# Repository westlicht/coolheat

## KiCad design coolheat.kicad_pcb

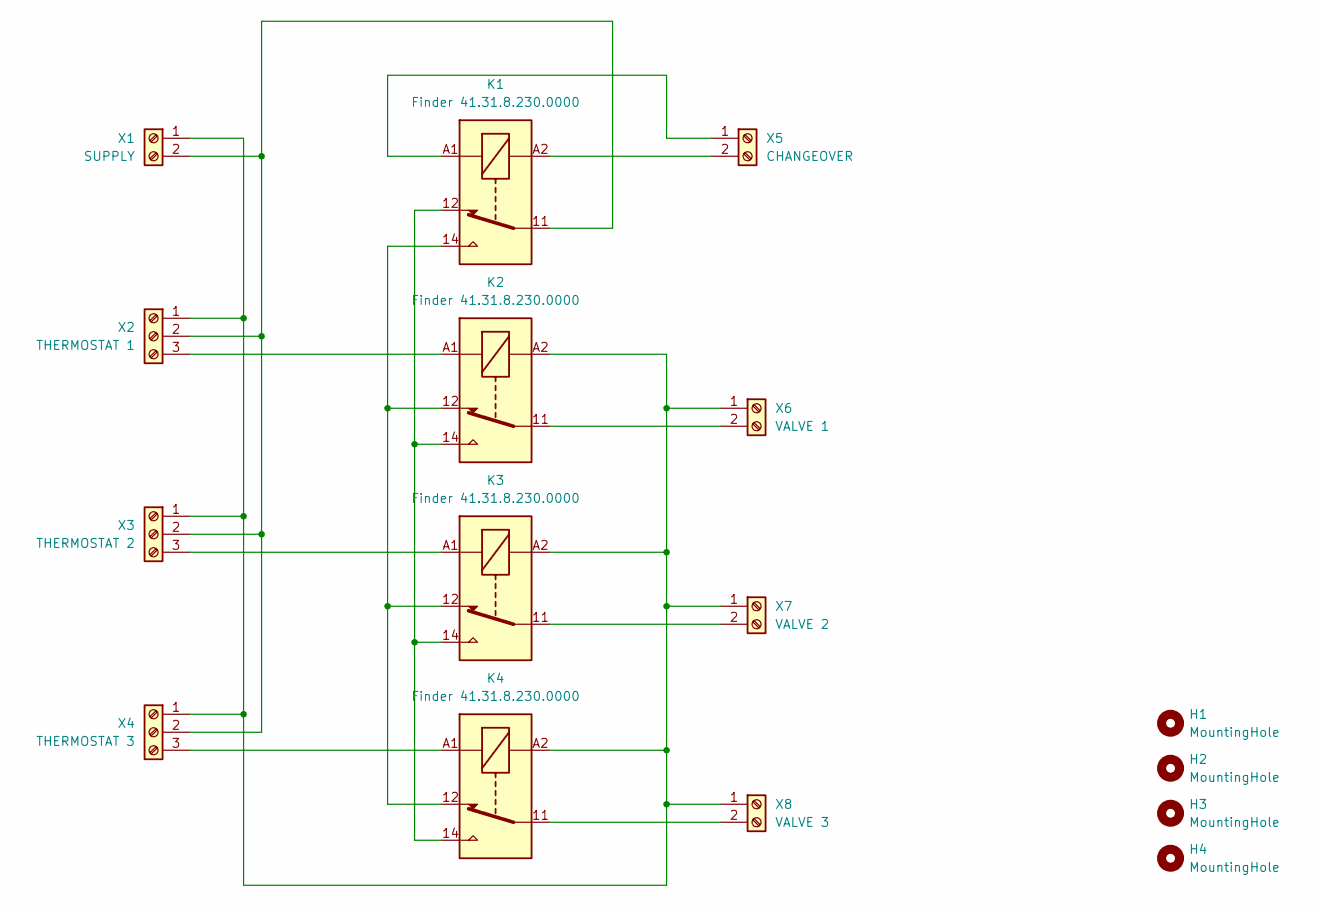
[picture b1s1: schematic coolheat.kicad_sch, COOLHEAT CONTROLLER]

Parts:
H1, H2, H3, H4: MountingHole; MountingHole_4.3mm_M4
K1, K2, K3, K4: Finder 41.31.8.230.0000; Relay_SPDT_Finder_41.31
X1: SUPPLY; TerminalBlock_Phoenix_MKDS-3-2-5.08_1x02_P5.08mm_Horizontal
X2: THERMOSTAT 1; TerminalBlock_Phoenix_MKDS-3-3-5.08_1x03_P5.08mm_Horizontal
X3: THERMOSTAT 2; TerminalBlock_Phoenix_MKDS-3-3-5.08_1x03_P5.08mm_Horizontal
X4: THERMOSTAT 3; TerminalBlock_Phoenix_MKDS-3-3-5.08_1x03_P5.08mm_Horizontal
X5: CHANGEOVER; TerminalBlock_Phoenix_MKDS-3-2-5.08_1x02_P5.08mm_Horizontal
X6: VALVE 1; TerminalBlock_Phoenix_MKDS-3-2-5.08_1x02_P5.08mm_Horizontal
X7: VALVE 2; TerminalBlock_Phoenix_MKDS-3-2-5.08_1x02_P5.08mm_Horizontal
X8: VALVE 3; TerminalBlock_Phoenix_MKDS-3-2-5.08_1x02_P5.08mm_Horizontal

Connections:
unnamed: K1.12, K2.14, K3.14, K4.14
unnamed: K1.14, K2.12, K3.12, K4.12
unnamed: K2.A2, K3.A2, K4.A2, X1.1, X2.1, X3.1, X4.1, X6.1, X7.1, X8.1
unnamed: K1.11, X1.2, X2.2, X3.2, X4.2
unnamed: K2.A1, X2.3
unnamed: K3.A1, X3.3
unnamed: K4.A1, X4.3
unnamed: K1.A1, X5.1
unnamed: K1.A2, X5.2
unnamed: K2.11, X6.2
unnamed: K3.11, X7.2
unnamed: K4.11, X8.2

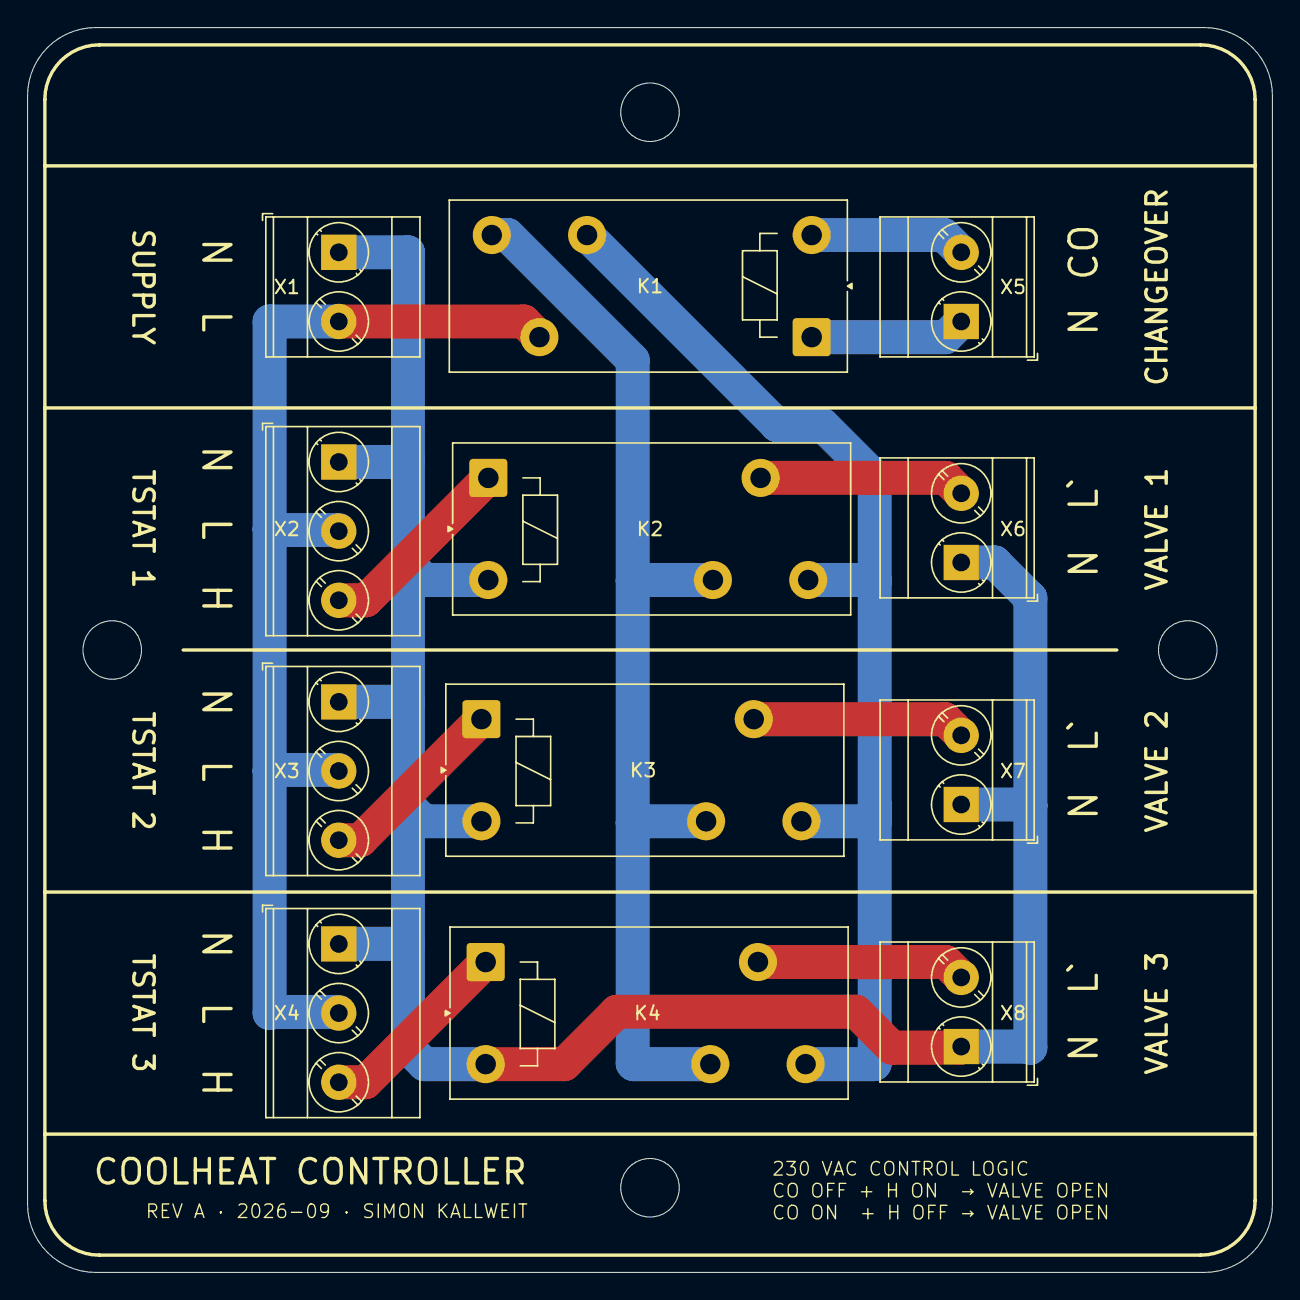
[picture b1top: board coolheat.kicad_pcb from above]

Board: 2 copper layers, 91.4 x 91.4 mm, 16 parts (0 on the bottom side), 12 nets.
